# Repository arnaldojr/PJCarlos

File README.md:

# Circuitos eletroeletrônicos: Fundamentos e desenvolvimento de projetos lógicos 

## Capítulo 8 - Prática ( Esquemático, Simulação e PCB) 

Parte prática da abordagem básica de sistemas numéricos, o desenvolvimento de uma placa de circuito impresso e de um projeto prático completo, a simulação virtual em 3D e a montagem final da placa eletrônica.

link:
https://www.amazon.com.br/Circuitos-Eletroeletr%C3%B4nicos-Fundamentos-Desenvolvimento-Projetos/dp/8536506687/ref=sr_1_8?qid=1572556299&refinements=p_27%3ARenato+Rodrigues+Paix%C3%A3o&s=books&sr=1-8

Circuitos eletroeletrônicos: Fundamentos e desenvolvimento de projetos lógicos - Renato Rodrigues Paixão / José Carlos de Souza Junior - 6 mar 2014

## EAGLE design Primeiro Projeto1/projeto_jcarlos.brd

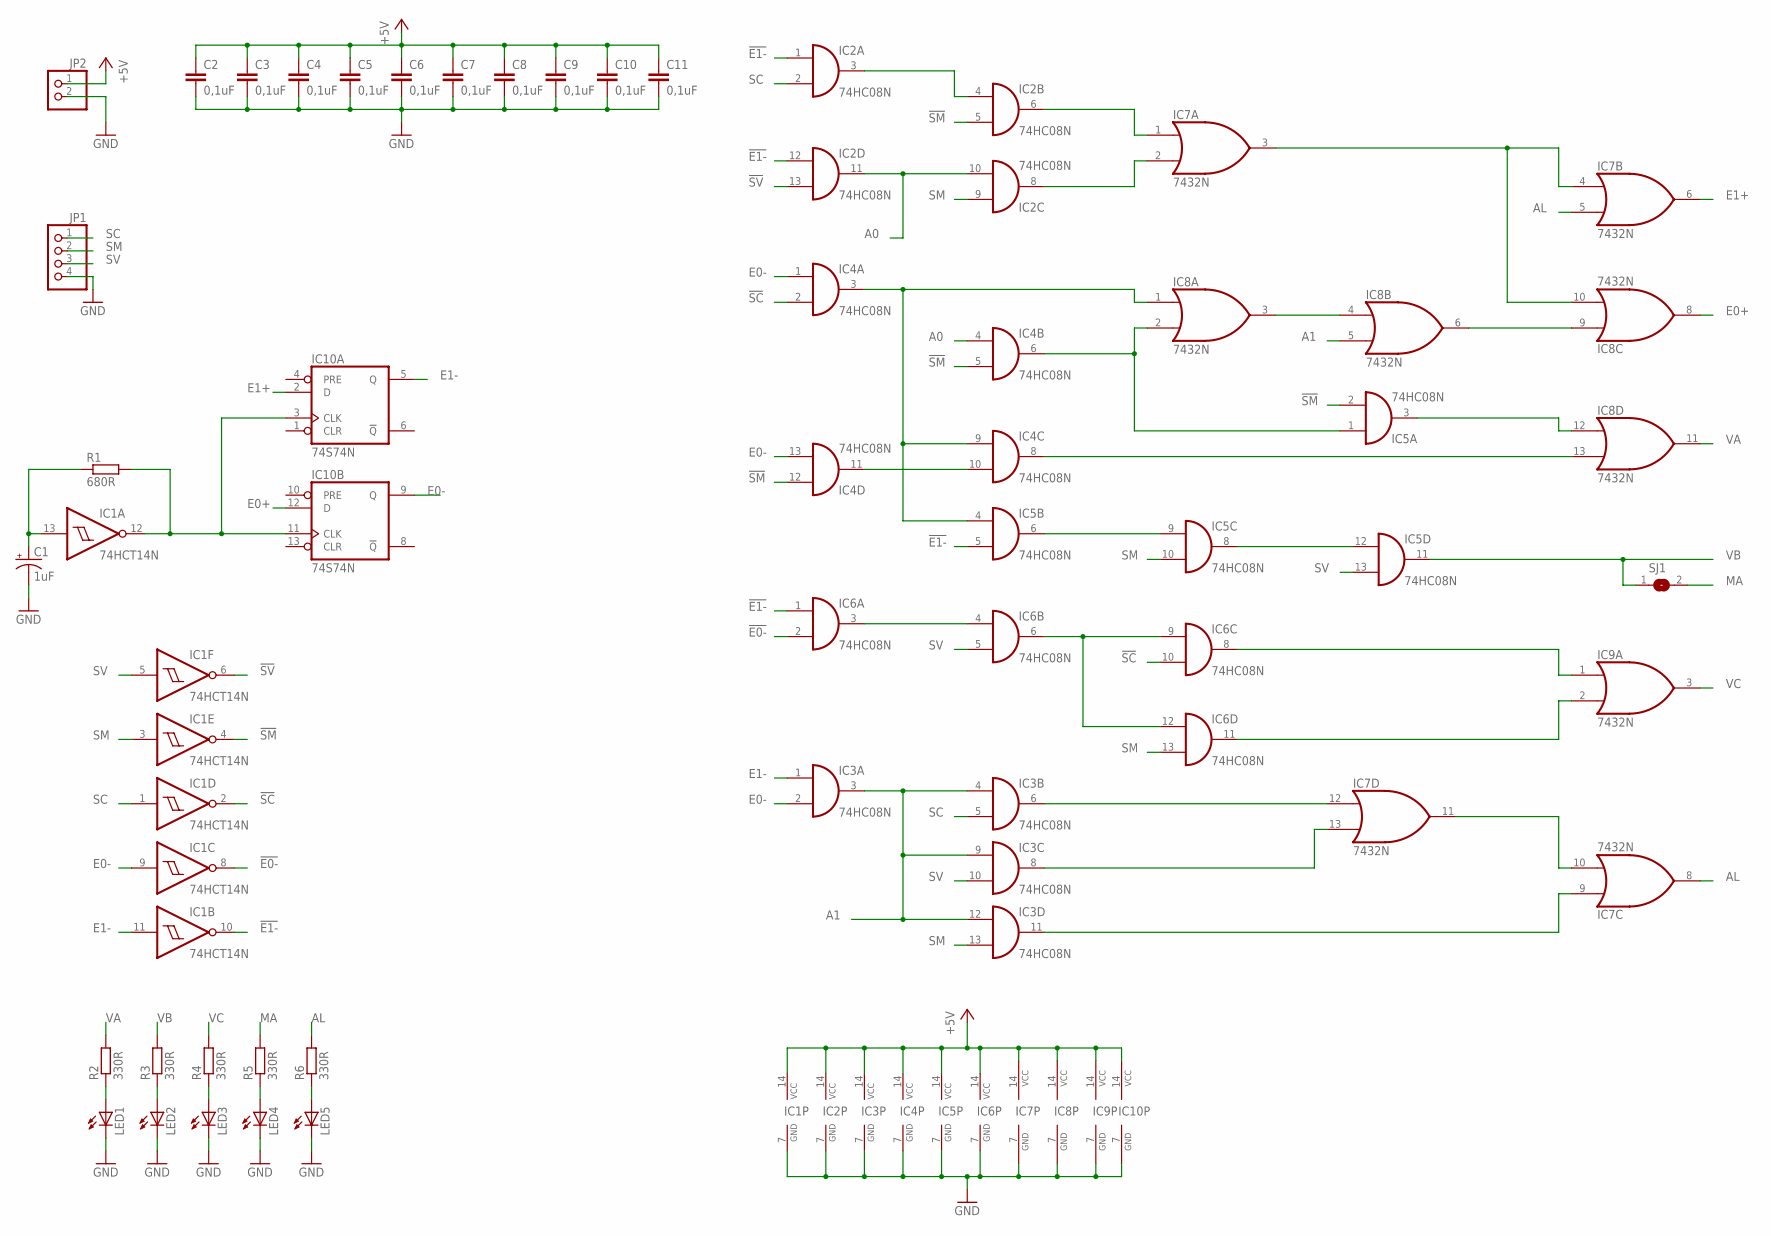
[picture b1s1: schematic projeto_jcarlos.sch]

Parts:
C1: 1uF; E2,5-5
C2, C3, C4, C5, C6, C7, C8, C9, C10, C11: 0,1uF; C025-025X050
IC1: 74HCT14N; DIL14
IC2, IC3, IC4, IC5, IC6: 74HC08N; DIL14
IC7, IC8, IC9: 7432N; DIL14
IC10: 74S74N; DIL14
JP1: PINHD-1X4; 1X04
JP2: PINHD-1X2; 1X02
LED1, LED2, LED3, LED4, LED5: LED5MM
R1: 680R; 0204/5
R2, R3, R4, R5, R6: 330R; 0204/5
SJ1: SJ

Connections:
!E0-: IC1.8 (O), IC6.2 (I1)
!E1-: IC1.10 (O), IC2.1 (I0), IC2.12 (I0), IC5.5 (I1), IC6.1 (I0)
!SC: IC1.2 (O), IC4.2 (I1), IC6.10 (I1)
!SM: IC1.4 (O), IC2.5 (I1), IC4.5 (I1), IC4.12 (I0), IC5.2 (I1)
!SV: IC1.6 (O), IC2.13 (I1)
+5V: C2.1, C3.1, C4.1, C5.1, C6.1, C7.1, C8.1, C9.1, C10.1, C11.1, IC1.14 (VCC), IC2.14 (VCC), IC3.14 (VCC), IC4.14 (VCC), IC5.14 (VCC), IC6.14 (VCC), IC7.14 (VCC), IC8.14 (VCC), IC9.14 (VCC), IC10.14 (VCC), JP2.1
A0: IC2.10 (I1), IC2.11 (O), IC4.4 (I0)
A1: IC3.3 (O), IC3.4 (I0), IC3.9 (I0), IC3.12 (I0), IC8.5 (I1)
AL: IC7.5 (I1), IC7.8 (O), R6.2
E0+: IC8.8 (O), IC10.12 (D)
E0-: IC1.9 (I), IC3.2 (I1), IC4.1 (I0), IC4.13 (I1), IC10.9 (Q)
E1+: IC7.6 (O), IC10.2 (D)
E1-: IC1.11 (I), IC3.1 (I0), IC10.5 (Q)
GND: C1.-, C2.2, C3.2, C4.2, C5.2, C6.2, C7.2, C8.2, C9.2, C10.2, C11.2, IC1.7 (GND), IC2.7 (GND), IC3.7 (GND), IC4.7 (GND), IC5.7 (GND), IC6.7 (GND), IC7.7 (GND), IC8.7 (GND), IC9.7 (GND), IC10.7 (GND), JP1.4, JP2.2, LED1.K (C), LED2.K (C), LED3.K (C), LED4.K (C), LED5.K (C)
MA: R5.2, SJ1.2
unnamed: IC5.6 (O), IC5.9 (I0)
unnamed: IC7.3 (O), IC7.4 (I0), IC8.10 (I1)
unnamed: IC4.10 (I1), IC4.11 (O)
unnamed: IC4.8 (O), IC8.13 (I1)
unnamed: IC8.3 (O), IC8.4 (I0)
unnamed: IC5.3 (O), IC8.12 (I0)
unnamed: C1.+, IC1.13 (I), R1.1
unnamed: IC1.12 (O), IC10.3 (CLK), IC10.11 (CLK), R1.2
unnamed: IC8.6 (O), IC8.9 (I0)
unnamed: IC4.3 (O), IC4.9 (I0), IC5.4 (I0), IC8.1 (I0)
unnamed: IC5.8 (O), IC5.12 (I0)
unnamed: IC4.6 (O), IC5.1 (I0), IC8.2 (I1)
unnamed: IC2.3 (O), IC2.4 (I0)
unnamed: LED1.A, R2.1
unnamed: IC2.6 (O), IC7.1 (I0)
unnamed: LED2.A, R3.1
unnamed: LED3.A, R4.1
unnamed: IC2.8 (O), IC7.2 (I1)
unnamed: IC3.6 (O), IC7.12 (I0)
unnamed: IC3.8 (O), IC7.13 (I1)
unnamed: IC3.11 (O), IC7.9 (I0)
unnamed: IC7.10 (I1), IC7.11 (O)
unnamed: LED4.A, R5.1
unnamed: LED5.A, R6.1
unnamed: IC6.3 (O), IC6.4 (I0)
unnamed: IC6.6 (O), IC6.9 (I0), IC6.12 (I0)
unnamed: IC6.8 (O), IC9.1 (I0)
unnamed: IC6.11 (O), IC9.2 (I1)
SC: IC1.1 (I), IC2.2 (I1), IC3.5 (I1), JP1.1
SM: IC1.3 (I), IC2.9 (I0), IC3.13 (I1), IC5.10 (I1), IC6.13 (I1), JP1.2
SV: IC1.5 (I), IC3.10 (I1), IC5.13 (I1), IC6.5 (I1), JP1.3
VA: IC8.11 (O), R2.2
VB: IC5.11 (O), R3.2, SJ1.1
VC: IC9.3 (O), R4.2

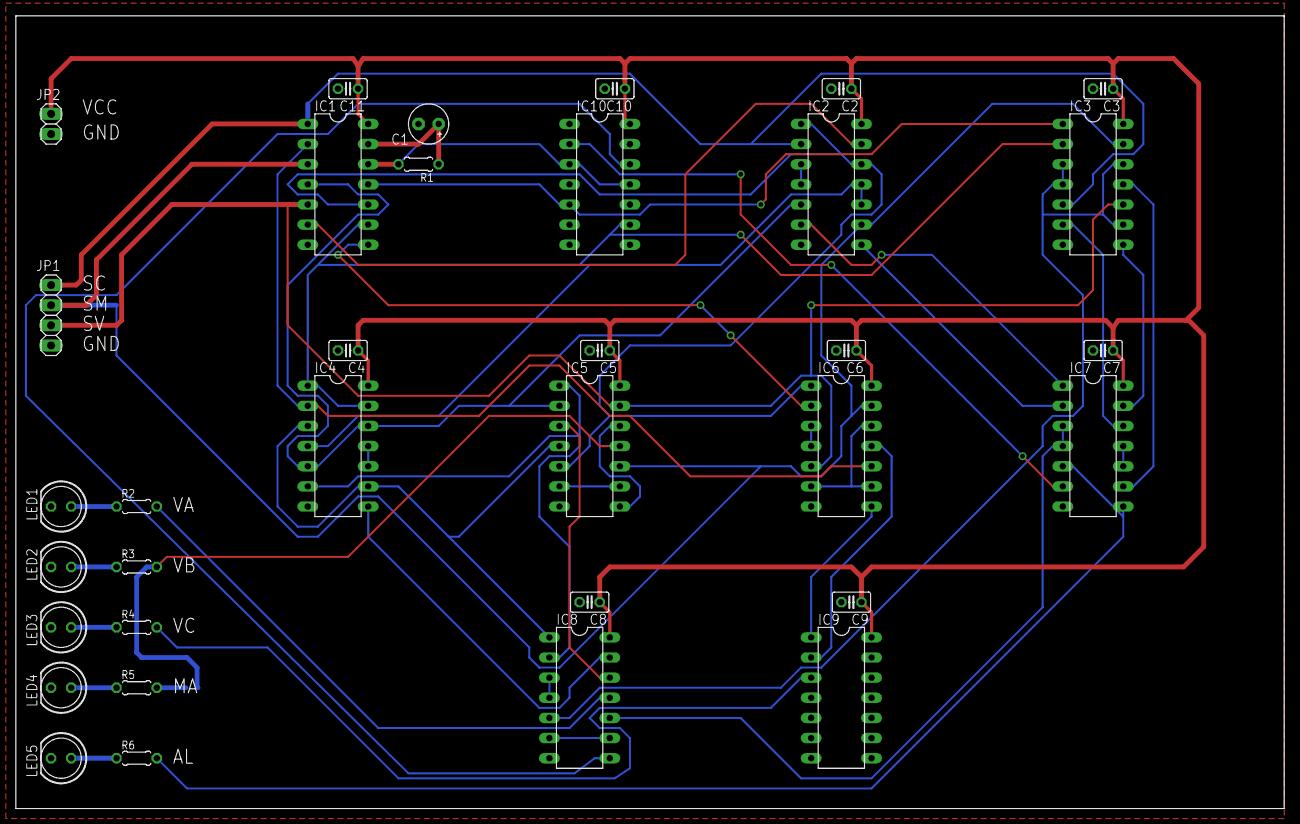
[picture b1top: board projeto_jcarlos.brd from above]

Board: 2 copper layers, 160.0 x 100.0 mm, 35 parts (1 on the bottom side), 49 nets.

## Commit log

2018-11-02 commit inicial
